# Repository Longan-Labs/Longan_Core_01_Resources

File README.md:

Resources of [Longan Core 01](https://www.longan-labs.cc/1040009.html)

Include:

1. Eagle File
2. Images
3. Drivers for CH340

Click on [Longan-Labs.cc](https://www.longan-labs.cc/) to get the product you need.

Contact [support@longan-labs.cc](support@longan-labs.cc) if you need help.

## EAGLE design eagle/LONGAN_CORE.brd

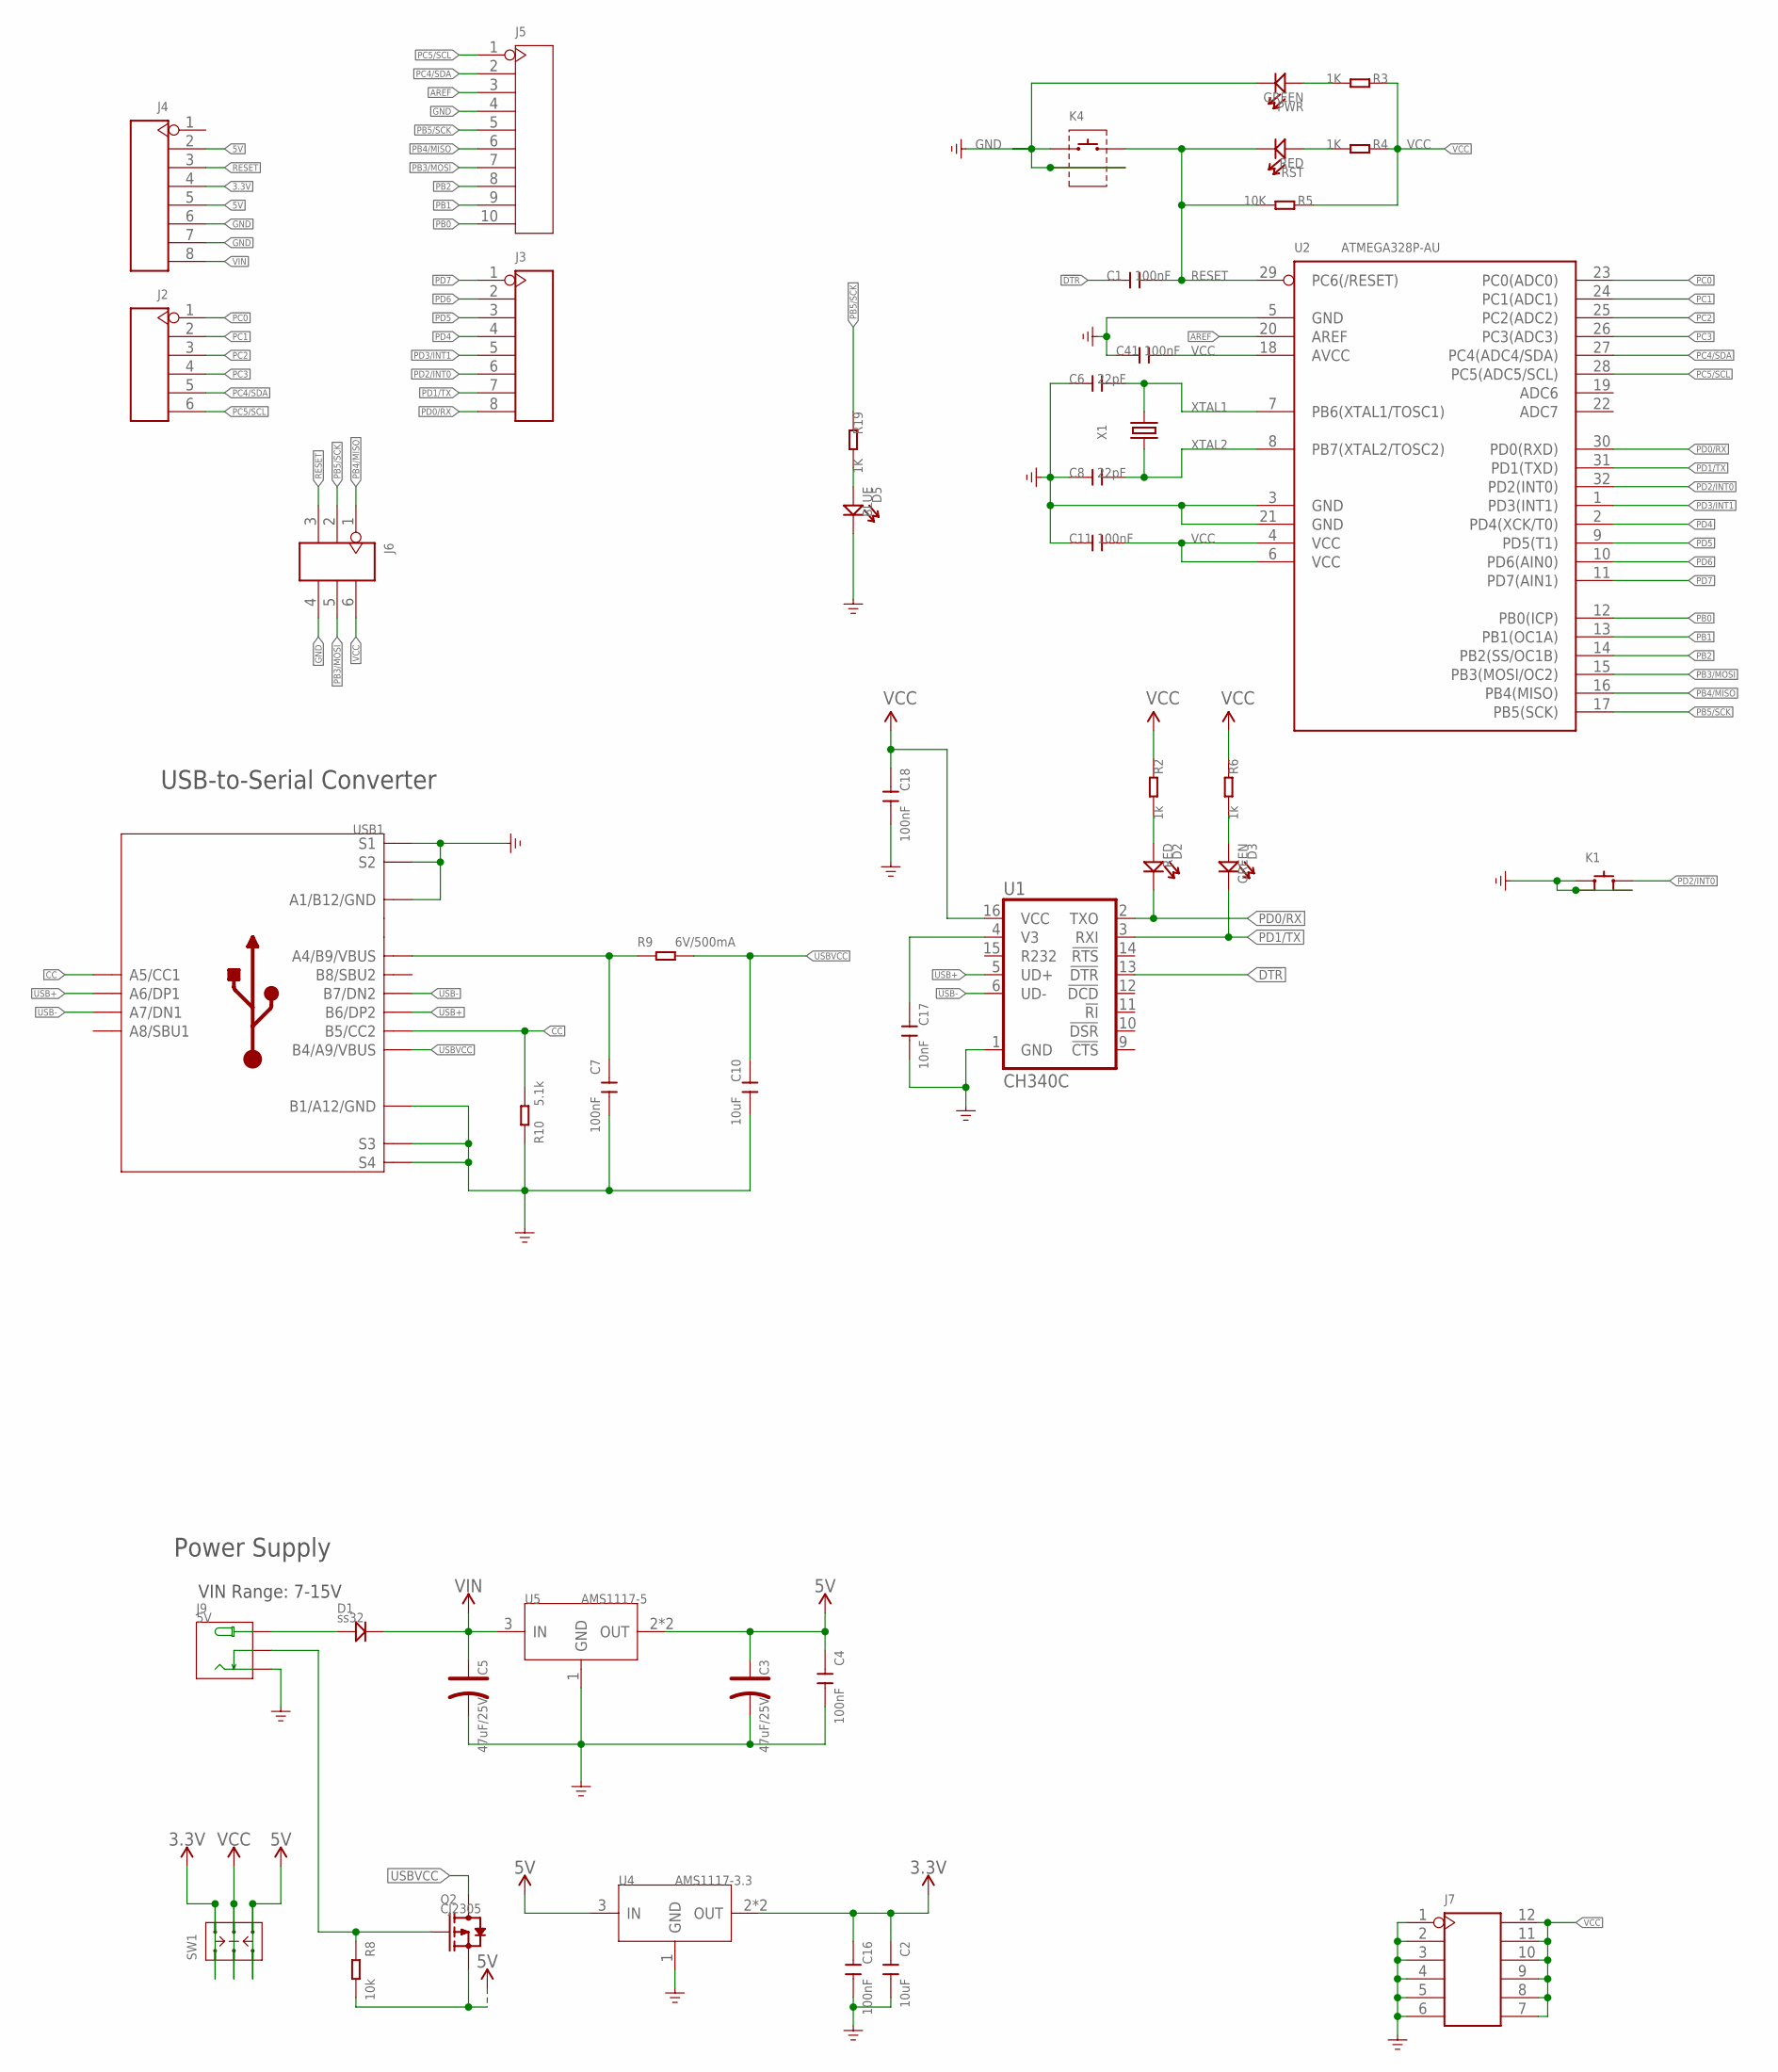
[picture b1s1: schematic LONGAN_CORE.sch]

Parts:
C1, C4, C7, C11, C16, C18, C41: 100nF; C0603
C2, C10: 10uF; C0603
C3, C5: 47uF/25V; ELECTRO-SMD-C-6MM
C6, C8: 22pF; C0603
C17: 10nF; C0603
D1: ss32; DO-214AC
D2: RED; LED-0603
D3: GREEN; LED-0603
D5: BLUE; LED-0603
J2: HEADER-6P-55/35MIL; H6-2.54
J3, J4: HEADER-8P-65/35MIL; H8-2.54-C65D35MIL
J5: HEADER-10P-2.54; H10-2.54
J6: HEADER-2X3P-2.54; H2X3-2.54
J7: HEADER-2X6P-2.54; H2X6-2.54
J9: 5V; DCJ3P-14.2X11.0X9.0MM
K1: BUTTON-4P-6.2X6.2; SW4-SMD-6.2X6.2MM
K4: BUTTON-2+2P; SW2+2P-7.7X2.75X3.95MM
PWR: GREEN; LED-0603
Q2: CJ2305; SOT-23
R2, R6: 1k; R0603
R3, R4, R19: 1K; R0603
R5: 10K; R0603
R8: 10k; R0603
R9: 6V/500mA; R0805
R10: 5.1k; R0603
RST: RED; LED-0603
SW1: SWITCH-2CH-6P-311010004; SW6-2.54-9.0X3.5X3.2+2.0MM
U1: CH340C; SO016
U2: ATMEGA328P-AU; TQFP32-0.8-7X7MM
U4: AMS1117-3.3; SOT-223
U5: AMS1117-5; SOT-223
USB1: TYPE-C-31-M-12; USB2.0-TYPE-C
X1: 16MHz; HC49US

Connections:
3.3V: C2.1, C16.1, J4.4, SW1.CH1A, SW1.CH2A, U4.2 (OUT), U4.TER (OUT)
5V: C3.+, C4.1, J4.2, J4.5, Q2.2 (S), R8.2, SW1.CH1B, SW1.CH2B, U4.3 (IN), U5.2 (OUT), U5.TER (OUT)
!DTR: C1.1, U1.13 (!DTR)
AREF: J5.3, U2.20 (AREF)
CC: R10.2, USB1.A5 (A5/CC1), USB1.B5 (B5/CC2)
GND: C2.2, C3.-, C4.2, C5.-, C6.1, C7.2, C8.1, C10.2, C11.1, C16.2, C17.2, C18.2, C41.1, D5.-, J4.6, J4.7, J5.4, J6.4, J7.1, J7.2, J7.3, J7.4, J7.5, J7.6, J9.-1 (-), K1.1 (A0), K1.3 (B1), K1.4 (A1), K4.1, K4.S1, K4.S2, PWR.-, R10.1, U1.1 (GND), U2.3 (GND), U2.5 (GND), U2.21 (GND), U4.1 (GND), U5.1 (GND), USB1.A1_B12 (A1/B12/GND), USB1.B1_A12 (B1/A12/GND), USB1.S1, USB1.S2, USB1.S3, USB1.S4, USB1.S5 (S1), USB1.S6 (S2)
INSERT: J9.-2 (CDN), Q2.1 (G), R8.1
unnamed: D5.+, R19.2
unnamed: C7.1, R9.1, USB1.A4_B9 (A4/B9/VBUS)
unnamed: D3.+, R6.2
unnamed: C17.1, U1.4 (V3)
unnamed: PWR.+, R3.2
unnamed: D2.+, R2.2
unnamed: R4.2, RST.+
PB0: J5.10, U2.12 (PB0(ICP))
PB1: J5.9, U2.13 (PB1(OC1A))
PB2: J5.8, U2.14 (PB2(SS/OC1B))
PB3/MOSI: J5.7, J6.5, U2.15 (PB3(MOSI/OC2))
PB4/MISO: J5.6, J6.1, U2.16 (PB4(MISO))
PB5/SCK: J5.5, J6.2, R19.1, U2.17 (PB5(SCK))
PC0: J2.1, U2.23 (PC0(ADC0))
PC1: J2.2, U2.24 (PC1(ADC1))
PC2: J2.3, U2.25 (PC2(ADC2))
PC3: J2.4, U2.26 (PC3(ADC3))
PC4/SDA: J2.5, J5.2, U2.27 (PC4(ADC4/SDA))
PC5/SCL: J2.6, J5.1, U2.28 (PC5(ADC5/SCL))
PD0/RX: D2.-, J3.8, U1.2 (TXO), U2.30 (PD0(RXD))
PD1/TX: D3.-, J3.7, U1.3 (RXI), U2.31 (PD1(TXD))
PD2/INT0: J3.6, K1.2 (B0), U2.32 (PD2(INT0))
PD3/INT1: J3.5, U2.1 (PD3(INT1))
PD4: J3.4, U2.2 (PD4(XCK/T0))
PD5: J3.3, U2.9 (PD5(T1))
PD6: J3.2, U2.10 (PD6(AIN0))
PD7: J3.1, U2.11 (PD7(AIN1))
PWRIN: D1.1 (+), J9.+
RESET: C1.2, J4.3, J6.3, K4.2, R5.2, RST.-, U2.29 (PC6(/RESET))
USB+: U1.5 (UD+), USB1.A6 (A6/DP1), USB1.B6 (B6/DP2)
USB-: U1.6 (UD-), USB1.A7 (A7/DN1), USB1.B7 (B7/DN2)
USBVCC: C10.1, Q2.3 (D), R9.2, USB1.B4_A9 (B4/A9/VBUS)
VCC: C11.2, C18.1, C41.2, J6.6, J7.7, J7.8, J7.9, J7.10, J7.11, J7.12, R2.1, R3.1, R4.1, R5.1, R6.1, SW1.COM1, SW1.COM2, U1.16 (VCC), U2.4 (VCC), U2.6 (VCC), U2.18 (AVCC)
VIN: C5.+, D1.2 (-), J4.8, U5.3 (IN)
XTAL1: C6.2, U2.7 (PB6(XTAL1/TOSC1)), X1.2
XTAL2: C8.2, U2.8 (PB7(XTAL2/TOSC2)), X1.1

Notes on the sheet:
USB-to-Serial Converter
Power Supply
VIN Range: 7-15V

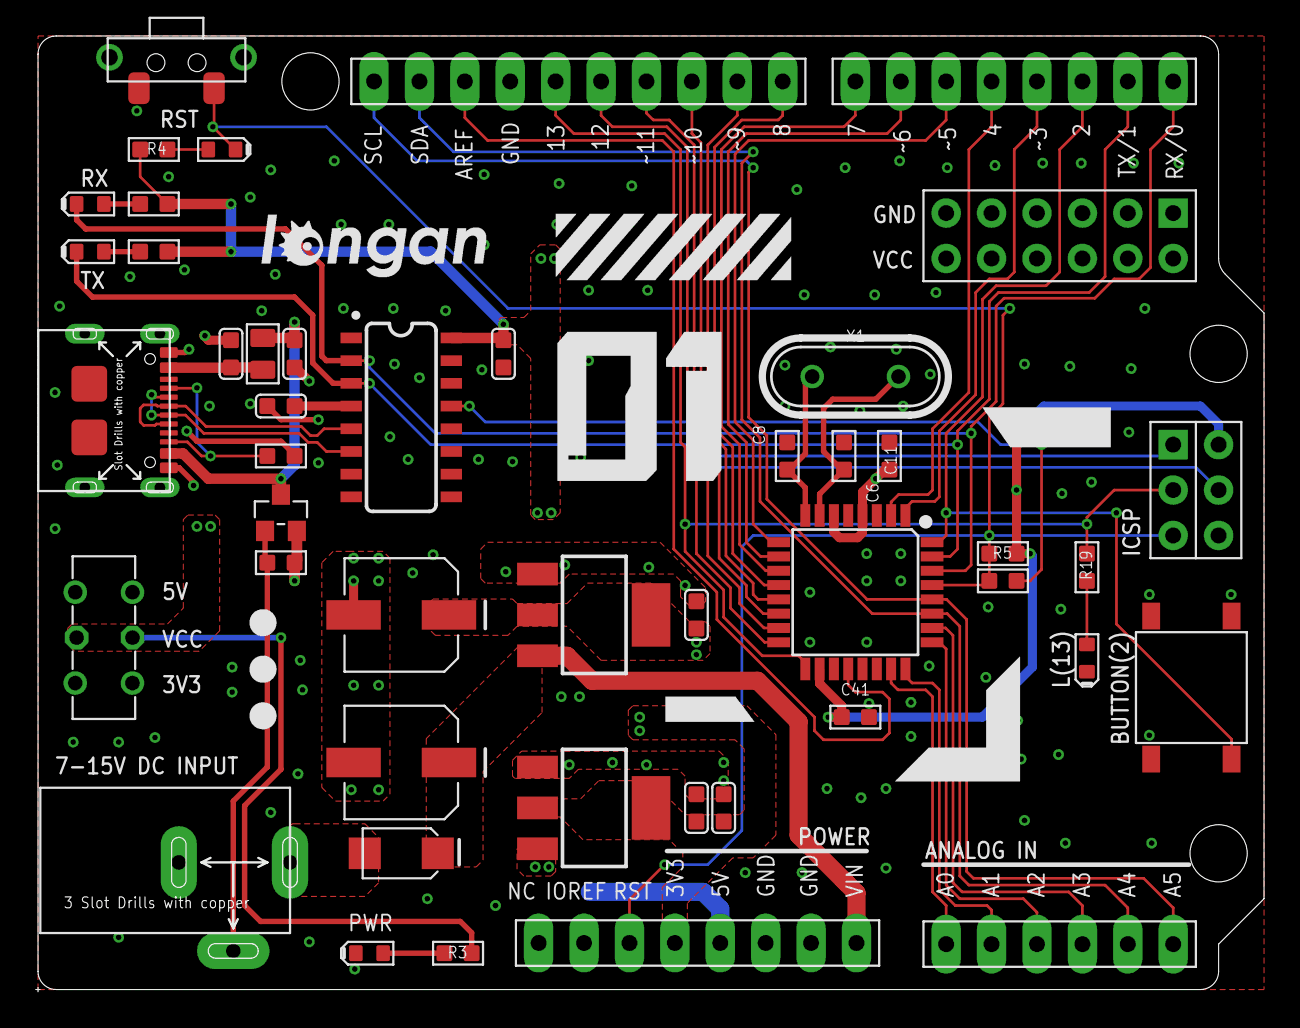
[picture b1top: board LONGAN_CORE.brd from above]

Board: 2 copper layers, 68.6 x 53.4 mm, 46 parts (0 on the bottom side), 43 nets.

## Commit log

2020-06-04 add images
2020-06-04 update image

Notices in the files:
parts and their libraries:
SparkFun-IC-Comms: Licensing: Creative Commons ShareAlike 4.0 International - https://creativecommons.org/licenses/by-sa/4.0
SparkFun-Aesthetics: Licensing: CC v3.0 Share-Alike You are welcome to use this library for commercial purposes.
